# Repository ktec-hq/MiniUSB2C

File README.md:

MiniUSB2C
Idea from https://github.com/manisteinn/usb-type-c-hhkb
MiniUSB2C is for some other keyboards that use MiniUSB like below.
先拆掉之前的MiniUSB，有热风枪比较好拆。

拆下后孔可以不用清理，找一些针焊上去。miniusb的5个脚的孔需要使用细一些的，我用的是二极管上剪的。下图这一面可以先焊上。

这一面的，先剪短了再焊上。

给USB Type-C的焊盘上锡（锡膏更好用），然后用风枪吹好，不要有粘连，要是有连上就用镊子给它划开一下，把多余的锡划走。

然后把Type-C的母座焊上，这里使用的是16p的母座。上机前务必用万用表测试一下键盘的VCC和GND没有短路，如果有短跳检查一下哪里没焊好，重新焊。

工作完美。

下面这个是本身已经焊好轴的PCB(YDPM40 demo green)，更换Type-C接口

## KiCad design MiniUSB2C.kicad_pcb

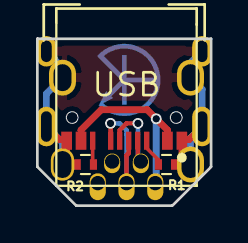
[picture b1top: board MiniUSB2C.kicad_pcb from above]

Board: 2 copper layers, 9.7 x 9.3 mm, 5 parts (1 on the bottom side), 6 nets.

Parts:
J1: USB; DX_USB
LOGO4: KTEC_LOGO; KTEC_Logo
R1, R2: 5k1; R_0402
USB1: USB_TYPE-C_16PIN; USB_TYPE-C_16PIN2

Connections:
/USB_D+: J1.3, USB1.6, USB1.8
/USB_D-: J1.2, USB1.5, USB1.7
GNDPWR: J1.5, J1.P$6, J1.P$7, J1.P$8, J1.P$9, R1.2, R2.2, USB1.0, USB1.1, USB1.12
unnamed: R1.1, USB1.4
unnamed: R2.1, USB1.10
VBUS: J1.1, USB1.2, USB1.11

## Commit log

2018-01-01 first ver
2018-02-03 smaller
2018-02-03 smaller smaller
2018-02-10 img and gerber
2018-02-10 more pics
2018-02-13 v3: add 5.1K for CC pin
